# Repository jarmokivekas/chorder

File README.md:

Chorder
=======

This repository is essentially a fork of the original SpiffChorder. Some
changes have been made to make the code compile with the latest version
of avr-gcc and the USB driver library has been updated to a recent more
recent version.

The code in this repository will use the Atmega8 as the microcontroller
platform for now.

Original readme:
================

Spaceman Spiff's Chording Keyboard Experiment (SpiffChorder for 
short) is free software; you can redistribute it and/or modify 
it under the terms of the OBDEV license, as found in the 
licence.txt file.
                                                              
SpiffChorder is distributed in the hope that it will be useful,    
but WITHOUT ANY WARRANTY; without even the implied warranty of
MERCHANTABILITY or FITNESS FOR A PARTICULAR PURPOSE.  See the 
OBDEV license for further details.
                                                              
Spaceman Spiff's Chording Keyboard Experiment (or SpiffChorder for short)
is an experimental platform for creating a USB chording keyboard. A
chording keyboard or Chorded keyboard is an input device where characters
can be typed by pressing multiple keys at the same time. A popular design 
is the 7-key chorder, where one key is used for each of the index finger, 
middle finger, ring finger and pinky, and 3 keys for the thumb. This can 
be used with either the left or right hand (or a chorder can be used for 
each hand, effectively doubling the typing speed).

For the latest information regarding the SpiffChorder, check the 
project homepage:

  http://symlink.dk/projects/spiffchorder/

and the wiki:

  http://chorder.cs.vassar.edu/spiffchorder/forside

Both the hardware design and software/firmware for the SpiffChorder
is open, and you can make modifications as you see fit. The license is 
based on Objective Development's license, which is now GPL, but with 
the addition that the hardware is documented and open as well.

Objective Development's AVR USB driver is a firmware-only implementation 
of the low speed USB standard (1.5Mbps) which can be used on cheap AVR 
microcontrollers from Atmel.

The hardware for the SpiffChorder is very simple, and consists mainly of 
an ATmega168, a 12MHz crystal, and a few passive components for interfacing 
with the USB port. Additionally, a number of keys are connected for the
chorder. For the current configuration, 7 keys are used, but for future
expansion an eigth input-line has been allocated for the normal chord
decoding, as well as 3 lines that will be mapped directly to keys or
functions (e.g. modifier keys or mouse-clicks for a pointing device).
Optionally 3 LEDs can be connected, intended to show the internal
state/mode of the SpiffChorder.

Legacy hardware
---------------

Because the original design of the SpiffChorder was based on ATmega8
instead of ATmega168, some builders have hardware platforms based on
ATmega8. For this reason it has been decided to try and keep compability
with the old ATmega8 design, with the limitations presented by the
smaller amount of flash memory for program storage. If you are 
constructing the SpiffChorder, use of the ATmega8 is discouraged, because
of code size constraints. One of the nice properties of the SpiffChorder
design is ability to use a USB bootloader, allowing the SpiffChorder
firmware to be updated over the existing USB connection. The bootloader
uses a 2kB bootblock, which leaves only 6kB for code on the ATmega8,
versus 14kB on the ATmega168. At the current stage the code for the
SpiffChorder is very close to the 6kB limit, so just getting a few of 
the planned additional features implemented will likely pass the boundary,
meaning that people with ATmega8-based hardware cannot use the bootloader.

Also, there are plans to extend the SpiffChorder into a composite device,
implementing both a (chording) keyboard and a pointing device, such as the
mini trackball from SparkFun:
http://www.sparkfun.com/commerce/product_info.php?products_id=755

With this addition the code will very likely be larger, even above the
8kB limit, so for this the ATmega168 will probably be the only way to 
go.

If, dispite these warnings, you want to compile the SpiffChorder 
firmware for ATmega8, this should be possible by simply changing the
MCU-line in the Makefile. In the places where hardware differences
influence the code, an attempt has been made to make conditional
code, compiling on the different platforms, based on the MCU selected
in the Makefile.

Since the ATmega8 is not officially supported, especially if changes
are made to the code, pay attention to the size of the code generated.
At the end of the build process you should see a dump of the different
sizes, like the following:
Size after:
main.elf  :
section            size      addr
.text              5904         0
.data                14   8388704
.bss                 76   8388718
.stab              5328         0
....

The number to look for is the size of the .text segment, in this case
5904 bytes. If using the ATmega8, you have 6144 bytes if using a 
bootloader and 8192 bytes otherwise.

Building the hardware
---------------------

The hardware for SpiffChorder is quite simple. Circuit diagrams are
included in the directory "circuit" in PDF and PNG formats. The USB
interface hardware is based on Mindaugas Milasauskas' MJoy application
(http://www.mindaugas.com/projects/MJoy/). Apart from that, the only
interesting things are the 12MHz crystal and interface to the 7 switches
and optionally 3 LEDs.

No circuit board layout is published, mainly because the application
is so simple that it is easier to realize on a perf-board (strip-board),
but the diagram should provide all needed information to create your own
implementation, whether on a perf-board or with printed circuit boards.

A bill of materials (BOM) can be found in circuit/bom.txt, along with some
additional notes regarding the chosen component values.

Building the firmware
---------------------

The SpiffChorder firmware requires avr-gcc and avr-libc (see 
http://www.nongnu.org/avr-libc/ for more details).

Before attempting to compile, edit the Makefile to select the
desired chord mapping and programmer options.

For the easiest approach, you can use WinAVR under Windows, which is
a bundle of the required libraries and tool-chain packaged for
Windows. It even comes with a good editor (Programmers Notepad),
which was used for the development throughout this project.
WinAVR is available from http://winavr.sourceforge.net/.

After installing WinAVR you should be able to run the command
"make" from the directory where the source code is located, which
will build the firmware. The "Makefile" included with the project is
based on an example from the WinAVR distribution, and has support
for burning the firmware to an AVR device through a range of different
programmers supported by the AVRdude programming utility. With a few
modifications to the Makefile it should be possible to accomplish this
programming by issuing the command "make program". Of course these
commands can also be executed from within Programmers Notepad.

Of course you will need some programming hardware to connect between
the circuit and the PC. Several possibilities exist (and are supported
by AVRdude), including some very simple programmers that can be built
on a tight budget. During the experimentation and development of this
project, I have used an STK500 development board from Atmel. If you 
have the possibility of getting one of these, I can highly recommend it,
not only as a programmer, but for a wealth of experiments that can be
done on the board, before any hardware needs to be built.

It is important that the fuses of the microcontroller are set correctly
before the application will work. The most important thing is to configure
the device to use an external crystal. The default configuration of the 
AVR device is to use the internal RC oscillator from the factory, but
this is not sufficiently accurate to handle the delicate timing required 
for USB communication. The Makefile has a target called fuses, 
which uses avrdude to set the fuses for the device (provided the avrdude 
settings in the Makefile have been configured in an appropriate way).

If your programmer does not work with avrdude, you should configure the
fuses as follows (hfuse=0xDD,lfuse=0xFF):
  * Boot flash size = 1024 words
  * Brown-out detection level = 2.7 V
  * External crystal 8.0MHz-xxMHz 16K CK/14 CK + 65ms startup
  * Remember to disable the CKDIV8.

I have had problems when setting the BOD-level to 4.3V, resulting in
Windows saying the device was not recogniced, only to properly detect
it a few seconds later. Setting the BOD-level to 2.7V seems to solve
this.

If using the legacy ATmega8 hardware, the fuses should be configured
as follows: Boot Flash size = 1024 words, BOD-level = 4.0V, BOD enabled,
External crystal, 16K CK + 64ms startup (hfuse=0xD9,lfuse=0x3F).

NOTE: The fuse settings shown here do not enable the bootloader, but
starts the SpiffChorder code directly. If a bootloader is used, you
should set the bootloader enable fuse also (which should be described
in the documentation regarding getting the bootloader in place).

Be aware that the firmware provided here does not use OBDEV's USB 
vendor ID, since this originally was not allowed to be used for HID 
devices. Instead a sepearte VID/PID-pair has been acquired for the
SpiffChorder. You may use this PID freely for SpiffChorders, even
when changing the chord mappings or function of the code.

Files
-----
readme.txt              This file.
changes.txt             What has been changed in the different versions.
doc.txt                 Extra documentation (for further development).
license.txt             The license this project is released under.
circuit/                Directory with circuit diagrams in PDF and PNG formats.
usbdrv/                 Directory with the AVR-USB driver and docs.
keymaps/                Keyboard maps (chord maps).
Makefile                Build instructions for GNU Make.
main.c                  Main source code file.
main.hex                Compiled version, ready to be programmed into uC.
usbconfig.h             Configuration for AVR-USB stack.

License information
-------------------

The SpiffChorder project is based on Objective Development's HIDkeys demo 
application, and although the restriction is mainly that any derivative
works should be published under an Open Source license, the additional
requirements by OBDEV are very resonable, and the entire project has
been released under this license. In other words you should feel free
to use the firmware here for any purpose, but any enhancements should
be given back to the community, in the form of a contribution to OBDEV's
project pages, with full documentation.

See the file license.txt for details.

Copyright
---------

The SpiffChorder project and documentation is Copyright (C) 2006-2008
by Mikkel Holm Olsen (AKA Spaceman Spiff). More information about the
project can be found on http://symlink.dk/projects/spiffchorder/.

$Id: readme.txt 12 2008-03-07 23:20:46Z  $

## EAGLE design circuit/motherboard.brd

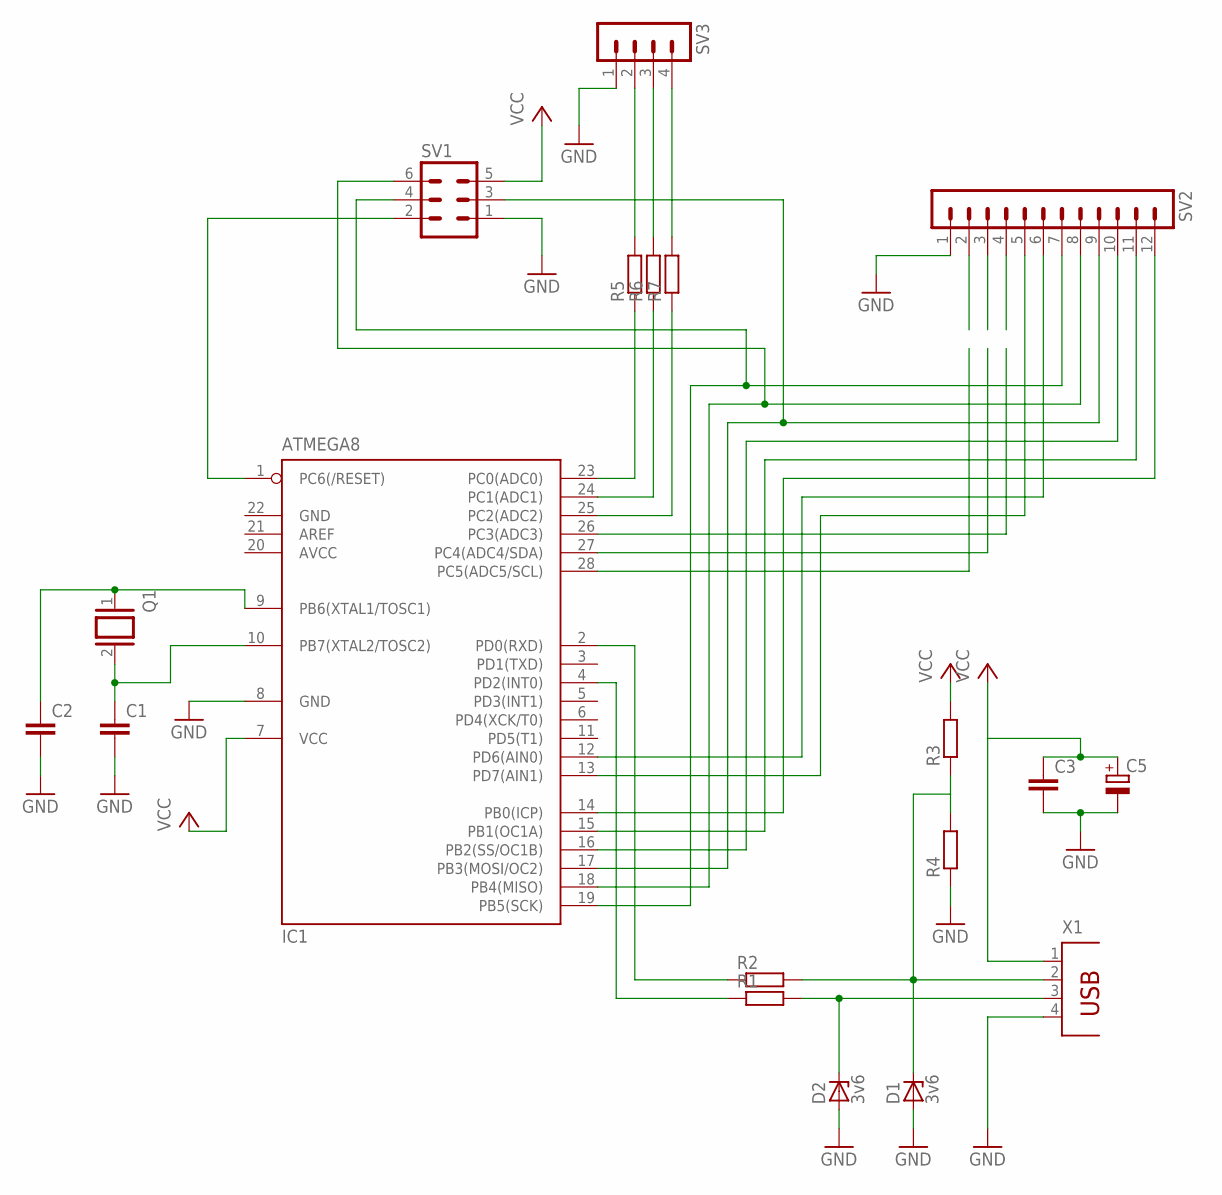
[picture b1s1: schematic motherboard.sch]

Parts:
C1, C2, C3: C-EU050-024X044; C050-024X044
C5: CPOL-EUB45181B; B45181B
D1, D2: 3v6; DO35Z10
IC1: ATMEGA8; DIL28-3
Q1: XTAL; Q
R1, R2, R3, R4: R-EU_0207/7; 0207/7
R5, R6, R7: R-EU_0204/7; 0204/7
SV1: MA03-2
SV2: MA12-1
SV3: MA04-1
X1: PN87520

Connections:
AVCC: IC1.20 (AVCC)
GND: C1.2, C2.2, C3.2, C5.-, D1.A, D2.A, IC1.8 (GND), IC1.22 (GND), R4.1, SV1.1, SV2.1, SV3.1, X1.4
unnamed: D1.C, R2.2, R3.1, R4.2, X1.2
unnamed: D2.C, R1.2, X1.3
unnamed: IC1.4 (PD2(INT0)), R1.1
unnamed: IC1.2 (PD0(RXD)), R2.1
unnamed: C1.1, IC1.10 (PB7(XTAL2/TOSC2)), Q1.2
unnamed: C2.1, IC1.9 (PB6(XTAL1/TOSC1)), Q1.1
unnamed: IC1.19 (PB5(SCK)), SV1.4, SV2.7
unnamed: IC1.14 (PB0(ICP)), SV2.12
unnamed: R5.2, SV3.2
unnamed: IC1.17 (PB3(MOSI/OC2)), SV1.3, SV2.9
unnamed: IC1.16 (PB2(SS/OC1B)), SV2.10
unnamed: IC1.15 (PB1(OC1A)), SV2.11
unnamed: IC1.12 (PD6(AIN0)), SV2.6
unnamed: IC1.13 (PD7(AIN1)), SV2.5
unnamed: IC1.1 (PC6(/RESET)), SV1.2
unnamed: R6.2, SV3.3
unnamed: IC1.25 (PC2(ADC2)), R7.1
unnamed: IC1.24 (PC1(ADC1)), R6.1
unnamed: IC1.23 (PC0(ADC0)), R5.1
unnamed: IC1.18 (PB4(MISO)), SV1.6, SV2.8
unnamed: R7.2, SV3.4
VCC: C3.1, C5.+, IC1.7 (VCC), R3.2, SV1.5, X1.1

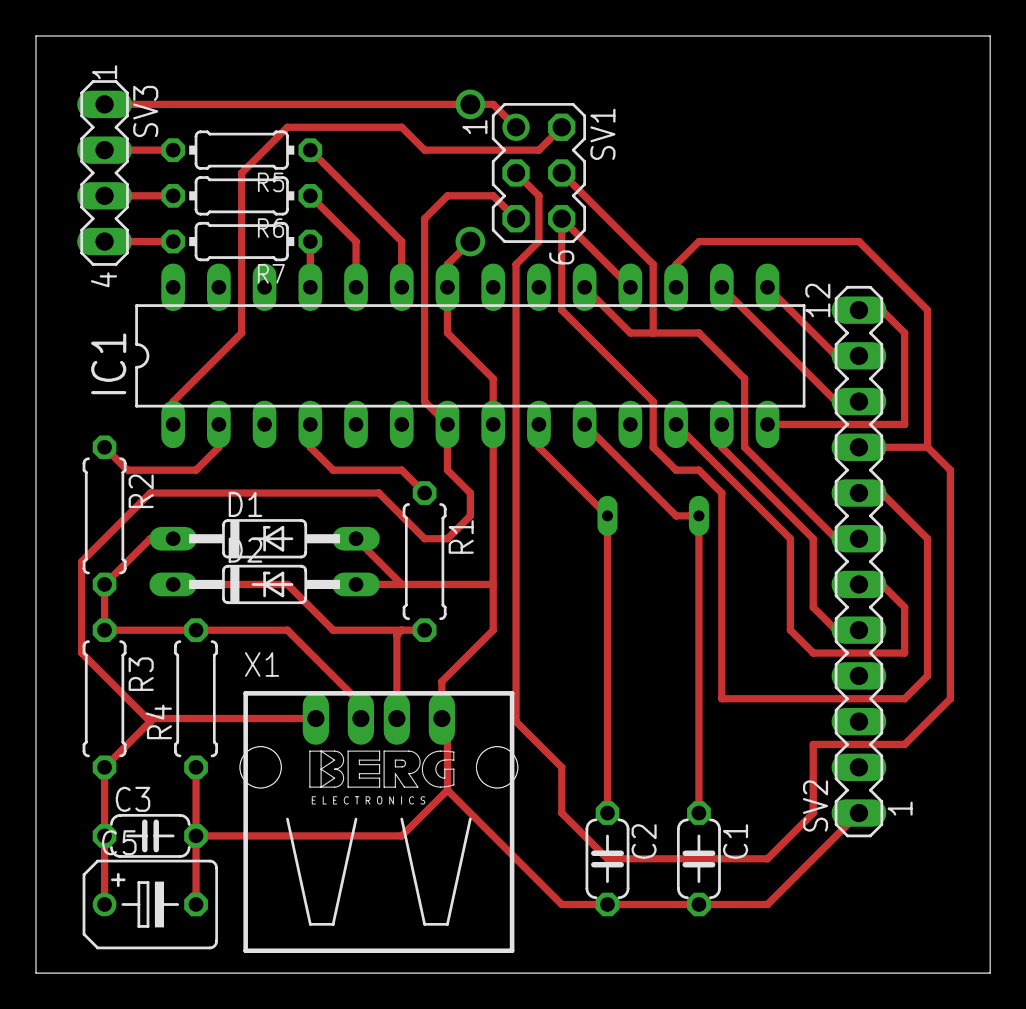
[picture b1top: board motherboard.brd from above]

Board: 2 copper layers, 53.0 x 52.1 mm, 19 parts (1 on the bottom side), 23 nets.

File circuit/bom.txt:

Bill of materials for SpiffChorder
----------------------------------

This document contains the list of components required to build
the SpiffChorder.

C1, C2                  22pF ceramic capacitor.
C3, C5                  100nF ceramic capacitor (decoupling).                
C4                      10uF electrolytic capacitor, min. 10V.               
CON1                    2x3 pin header, e.g. shrouded header from Harting.   
CON2                    USB connector, alternatively cable with type-A plug. 
CON3                    Connection to switches. Can be wired directly.       
CON4                    Connection to LEDs. Optional.                        
D1, D2                  3.6V zener-diode.                                    
IC1                     Atmel ATmega168.                                       
R1                      2.2 kOhm resistor.                                   
R2                      4.7 kOhm resistor.                                   
R3, R4                  82 Ohm resistor.                                     
R5-R7                   LED current limiting resistors. About 1 kOhm,        
                        depending on selected LEDs.                          
R8-R18                  Optional pull-up resistors. 10 kOhm or 4.7 kOhm.     
X1                      12.000 MHz crystal.                                  


NOTES:
 * C1 and C2 should ideally match the load capacitance Cl of the crystal X1.
   If Cl is not known, 22pF for C1 and C2 seems to work.
 * CON1 is for in-system programming. If a socket is used for the ATmega168,
   this is not needed. Also, current implementations of the SpiffChorder
   allows the use of a boot loader working over the existing USB connection.
   This allows the firmware to be updated without special programming 
   hardware. But the boot loader needs to be installed in the ATmega168 before
   it is soldered in place (unless the CON1 connector is mounted).
 * CON2 is a USB connector. Use either a type-B receptacle, in combination
   with a USB type-A to type-B cable. Or find a USB cable with a type-A plug
   in one end, and cut off the other end. The schematics show the standard
   colors for the USB connections.
 * CON3 if for connecting the switches. A connector is not needed, as the
   switches can be wired directly. Each switch should connect one of the
   inputs to ground when pressed. In other words a normally open (NO) type 
   switch should be used.
 * CON4 provides the connection to 3 status LEDs. These show the current mode
   of the SpiffChorder, and are therefore optional. Again the LEDs can be 
   wired directly, no connector is needed. If the LEDs are not mounted, the
   current limiting resistors R5-R7 can be omitted as well.
 * IC1 is the ATmega168. The schematics show the pin-numbering for the P version
   (DIL package). If using the SMD version, use the pin-names instead. The 
   ATmega168V should not be used, as it does not support running at 12MHz.
   I have used ATmega168-20PI, which is RoHS compatible, but the older 
   ATmega168-20PU works equally well.
 * R5-R7 are current limiting resistors for the (optional) LEDs. The value 
   of these depend on how bright the LEDs should be, and the voltage drop
   across the LED. For newer LEDs, a value of 1 kOhm seems to give plenty of
   light, but you can go as low as 220 Ohm, resulting in about 20 mA current 
   through each LED. Note that this is a considerable amount of current 
   compared to the rest of the SpiffChorder.
 * R8-R18 are optional pull-up resistors. These should only be needed if the
   wires between the microcontroller and the switches are excessively long.
   A value of 10 kOhm or 4.7 kOhm should work, but remember that the lower
   the value, the greater the current consumption when the switch is pressed.
   Also, of not all switches are used, the extra pull-ups are not needed
   either.
   
 $Id: bom.txt 8 2008-03-02 18:34:57Z  $

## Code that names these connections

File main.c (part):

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/* Hardware documentation:
 * ATmega168 @12.000 MHz
 *
 * PB0     : Pinky key
 * PB1     : Ring finger key
 * PB2     : Middle finger key
 * PB3     : Index finger key
 * PB4     : Near thumb
 * PB5     : Center thumb
 * PB6..PB7: 12MHz X-tal
 * PC0     : Near LED
 * PC1     : Center LED
 * PC2     : Far LED
 * PC3     : Unused modifier 1
 * PC4     : Unused modifier 2
 * PC5     : Unused modifier 3
 * PD0     : D- USB negative (needs appropriate zener-diode and resistors)
 * PD1     : UART TX
 * PD2/INT0: D+ USB positive (needs appropriate zener-diode and resistors)
 * PD6     : Far thumb
 * PD7     : Extra chord button (unused)
 *
 * USB Connector:
 * -------------
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 *                  +--[4k7]--+--[2k2]--+
 *      USB        GND        |                     ATmega-8
 *                            |
 *      (D-)-------+----------+--------[82r]------- PD0
 *                 |
 *      (D+)-------|-----+-------------[82r]------- PD2/INT0
 *                 |     |
 *                 _     _
 *                 ^     ^  2 x 3.6V 
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  PORTB = 0x3F;   /* Enable pull-ups */
  DDRB  = 0x00;   /* Port B are switch inputs */

  PORTC = 0x38;   /* LEDs on PC0..PC2, switches on PC3..PC5 */
  DDRC  = 0x07;   /* PC0..PC2 are outputs, PC3..PC5 are inputs */
  
  PORTD = 0xfa;   /* 1111 1010 bin: activate pull-ups except on USB lines */
  DDRD  = 0x07;   /* 0000 0111 bin: all pins input except USB (-> USB reset) */
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
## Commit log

2014-04-10 change to new usb library
2014-04-10 remove compile errors
2014-04-16 add build files to .gitignore
2014-04-16 populate README.md
2014-04-16 remove project files from tracking
2014-06-02 add proto_1_body_flat.svg
2014-06-02 add stl to gitignore
2014-06-02 move thing in /mechanical
2014-06-02 Added lots of SVGs and SCADs
2014-11-05 add mechanical to tracking
2014-11-05 add schematic for board to tracking
2014-11-05 worked on proto SVGs
2014-11-05 edit .gitignore
2014-11-05 PCB layout done, add to tracking
2014-11-05 Fix messed up git repo
2014-11-05 millable png files made. Traces, holes, and outlines separately
2014-11-05 a couple of design rule checks fixed (not all)
2014-11-05 New PCB design, minor chenges in schematic
2014-11-05 remove unnecessary files in /mechanical, add some untracked files to tracking
2014-11-05 add motherboard file for etching

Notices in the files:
main.c:
SpiffChorder is Copyright (C) 2006-2008 Mikkel Holm Olsen
